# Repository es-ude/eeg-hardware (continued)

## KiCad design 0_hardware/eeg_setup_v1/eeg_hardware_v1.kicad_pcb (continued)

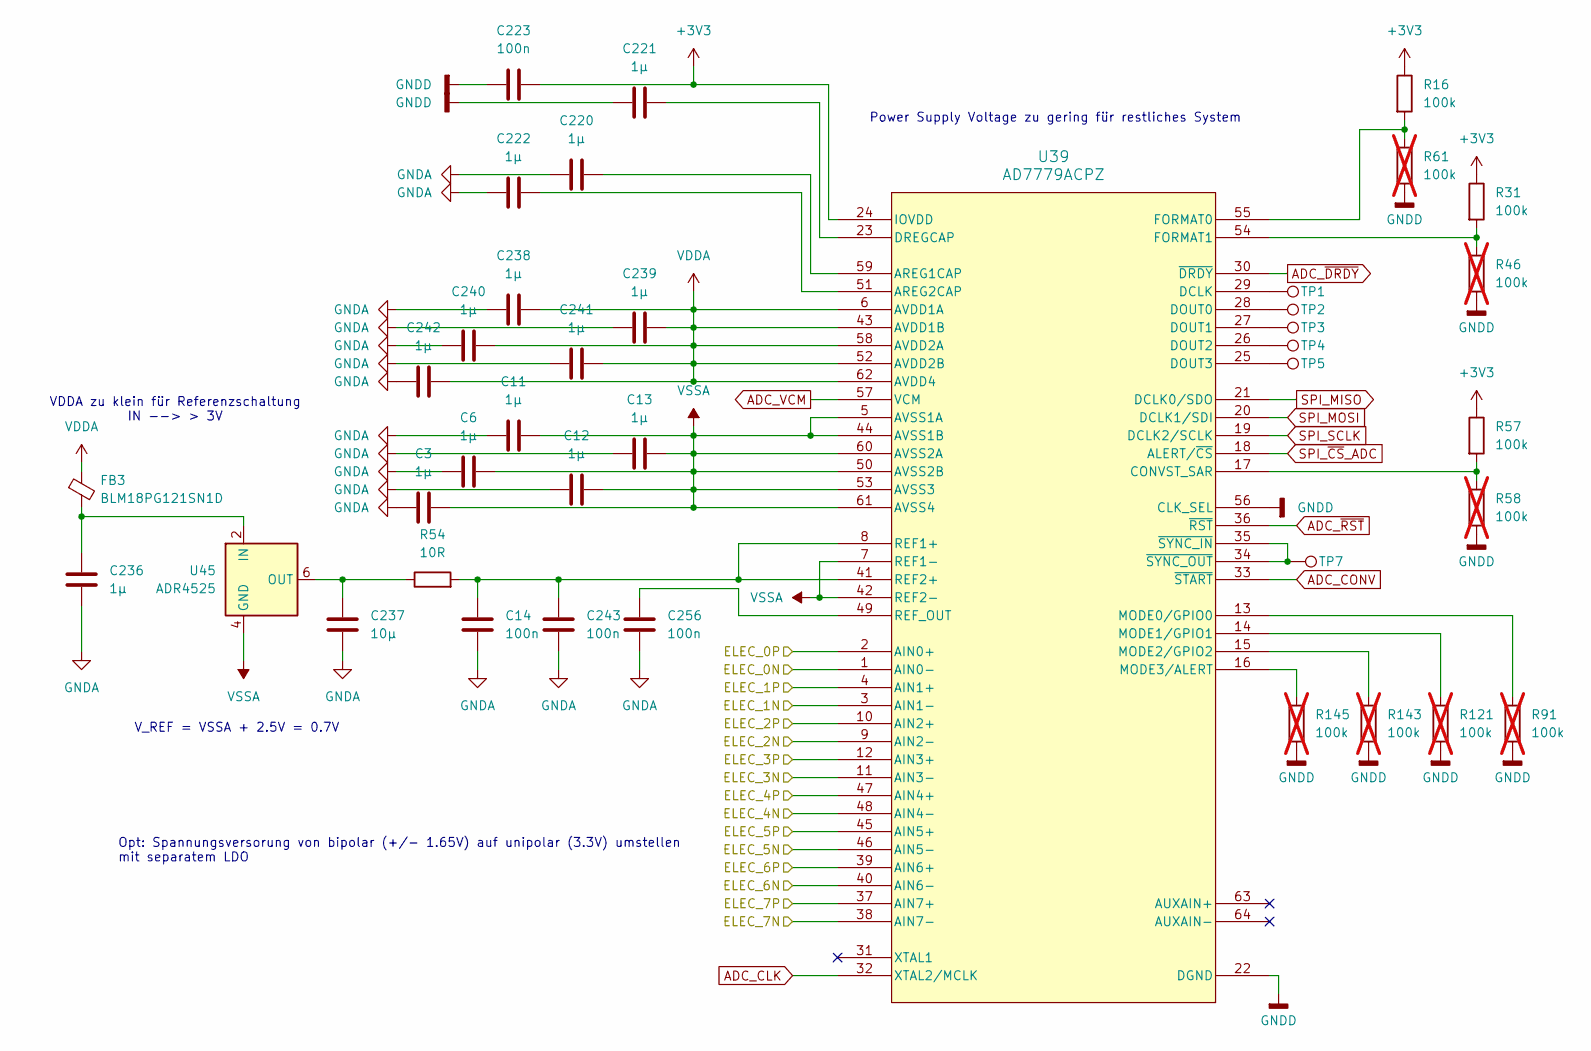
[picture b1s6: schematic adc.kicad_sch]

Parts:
C3, C6, C11, C12, C13, C220, C221, C222, C236, C238, C239, C240, C241, C242: 1µ; C_0603_1608Metric
C14, C223, C243, C256: 100n; C_0603_1608Metric
C237: 10µ; C_0603_1608Metric
FB3: FB_120Z_2A_0603; L_0603_1608Metric; MPN BLM18PG121SN1D
R16, R31, R57: 100k; R_0603_1608Metric
R46, R58, R61, R91, R121, R143, R145: 100k; R_0603_1608Metric; not fitted
R54: 10R; R_0603_1608Metric
TP1, TP2, TP3, TP4, TP5, TP7: TestPoint; TestPoint_Pad_1.5x1.5mm
U39: AD7779ACPZ; LFCSP-64-1EP_9x9mm_P0.5mm_EP5.21x5.21mm_ThermalVias
U45: ADR4525; SOIC-8_3.9x4.9mm_P1.27mm

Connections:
+3V3: C223.2, R16.1, R31.1, R57.1, U39.24 (IOVDD); also elsewhere on the board
/ADC/ELEC_0N: U39.1 (AIN0-); also elsewhere on the board
/ADC/ELEC_0P: U39.2 (AIN0+); also elsewhere on the board
/ADC/ELEC_1N: U39.3 (AIN1-); also elsewhere on the board
/ADC/ELEC_1P: U39.4 (AIN1+); also elsewhere on the board
/ADC/ELEC_2N: U39.9 (AIN2-); also elsewhere on the board
/ADC/ELEC_2P: U39.10 (AIN2+); also elsewhere on the board
/ADC/ELEC_3N: U39.11 (AIN3-); also elsewhere on the board
/ADC/ELEC_3P: U39.12 (AIN3+); also elsewhere on the board
/ADC/ELEC_4N: U39.48 (AIN4-); also elsewhere on the board
/ADC/ELEC_4P: U39.47 (AIN4+); also elsewhere on the board
/ADC/ELEC_5N: U39.46 (AIN5-); also elsewhere on the board
/ADC/ELEC_5P: U39.45 (AIN5+); also elsewhere on the board
/ADC/ELEC_6N: U39.40 (AIN6-); also elsewhere on the board
/ADC/ELEC_6P: U39.39 (AIN6+); also elsewhere on the board
/ADC/ELEC_7N: U39.38 (AIN7-); also elsewhere on the board
/ADC/ELEC_7P: U39.37 (AIN7+); also elsewhere on the board
ADC_CLK: U39.32 (XTAL2/MCLK); also elsewhere on the board
ADC_CONV: U39.33 (~START); also elsewhere on the board
ADC_VCM: U39.57 (VCM); also elsewhere on the board
ADC_~DRDY: U39.30 (~DRDY); also elsewhere on the board
ADC_~RST: U39.36 (~RST); also elsewhere on the board
GNDA: C3.1, C6.1, C11.1, C12.2, C13.2, C14.1, C220.2, C222.2, C236.2, C237.2, C238.1, C239.2, C240.1, C241.2, C242.1, C243.1, C256.1; also elsewhere on the board
GNDD: C221.2, C223.1, R46.2, R58.2, R61.2, R91.2, R121.2, R143.2, R145.2, U39.22 (DGND), U39.56 (CLK_SEL); also elsewhere on the board
unnamed: C220.1, U39.59 (AREG1CAP)
unnamed: C222.1, U39.51 (AREG2CAP)
unnamed: R57.2, R58.1, U39.17 (CONVST_SAR)
unnamed: TP1.1, U39.29 (DCLK)
unnamed: TP2.1, U39.28 (DOUT0)
unnamed: TP3.1, U39.27 (DOUT1)
unnamed: TP4.1, U39.26 (DOUT2)
unnamed: TP5.1, U39.25 (DOUT3)
unnamed: C221.1, U39.23 (DREGCAP)
unnamed: R16.2, R61.1, U39.55 (FORMAT0)
unnamed: R31.2, R46.1, U39.54 (FORMAT1)
unnamed: R91.1, U39.13 (MODE0/GPIO0)
unnamed: R121.1, U39.14 (MODE1/GPIO1)
unnamed: R143.1, U39.15 (MODE2/GPIO2)
unnamed: R145.1, U39.16 (MODE3/ALERT)
unnamed: C14.2, C243.2, R54.2, U39.8 (REF1+), U39.41 (REF2+)
unnamed: C256.2, U39.49 (REF_OUT)
unnamed: TP7.1, U39.34 (~SYNC_OUT), U39.35 (~SYNC_IN)
unnamed: C236.1, FB3.2, U45.2 (IN)
unnamed: C237.1, R54.1, U45.6 (OUT)
SPI_MISO: U39.21 (DCLK0/SDO); also elsewhere on the board
SPI_MOSI: U39.20 (DCLK1/SDI); also elsewhere on the board
SPI_SCLK: U39.19 (DCLK2/SCLK); also elsewhere on the board
SPI_~CS_ADC: U39.18 (ALERT/~CS); also elsewhere on the board
VDDA: C238.2, C239.1, C240.2, C241.1, C242.2, FB3.1, U39.6 (AVDD1A), U39.43 (AVDD1B), U39.52 (AVDD2B), U39.58 (AVDD2A), U39.62 (AVDD4); also elsewhere on the board
VSSA: C3.2, C6.2, C11.2, C12.1, C13.1, U39.5 (AVSS1A), U39.7 (REF1-), U39.42 (REF2-), U39.44 (AVSS1B), U39.50 (AVSS2B), U39.53 (AVSS3), U39.60 (AVSS2A), U39.61 (AVSS4), U39.65 (EP(GND)), U45.4 (GND); also elsewhere on the board

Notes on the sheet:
Power Supply Voltage zu gering für restliches System
Opt: Spannungsversorung von bipolar (+/- 1.65V) auf unipolar (3.3V) umstellen mit separatem LDO
VDDA zu klein für Referenzschaltung IN --> > 3V
V_REF = VSSA + 2.5V = 0.7V

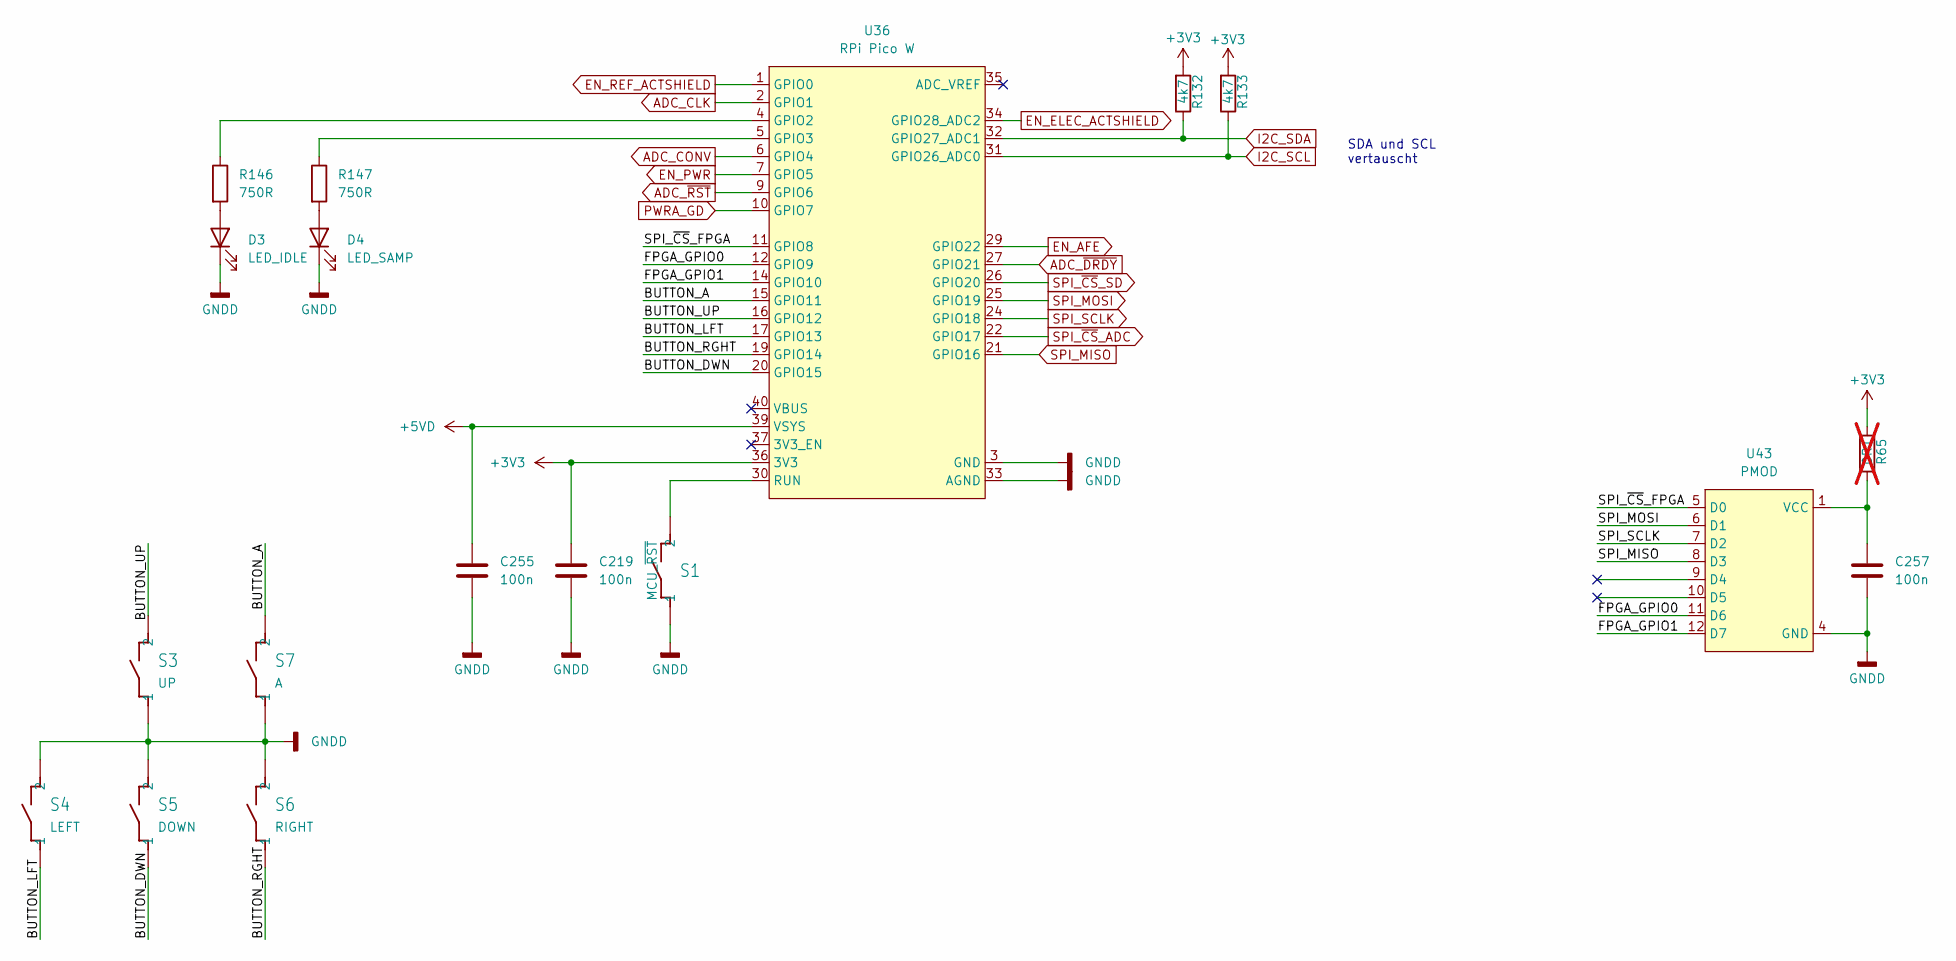
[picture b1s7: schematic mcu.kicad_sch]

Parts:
C219, C255, C257: 100n; C_0603_1608Metric
D3: LED_IDLE; LED_0603_1608Metric
D4: LED_SAMP; LED_0603_1608Metric
R65: 0R1; R_0603_1608Metric; not fitted
R132, R133: 4k7; R_0603_1608Metric
R146, R147: 750R; R_0603_1608Metric
S1: MCU_~{RST}; TACTILE-SWITCH
S3: UP; TACTILE-SWITCH
S4: LEFT; TACTILE-SWITCH
S5: DOWN; TACTILE-SWITCH
S6: RIGHT; TACTILE-SWITCH
S7: A; TACTILE-SWITCH
U36: RPi Pico W; RPi_PicoW
U43: PMOD; PinHeader_2x06_P2.54mm_Horizontal

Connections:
+3V3: C219.1, R65.2, R132.2, R133.2, U36.36 (3V3); also elsewhere on the board
+5VD: C255.1, U36.39 (VSYS); also elsewhere on the board
/MCU/BUTTON_A: S7.3 (2), S7.4 (2), U36.15 (GPIO11)
/MCU/BUTTON_DWN: S5.1, S5.2 (1), U36.20 (GPIO15)
/MCU/BUTTON_LFT: S4.1, S4.2 (1), U36.17 (GPIO13)
/MCU/BUTTON_RGHT: S6.1, S6.2 (1), U36.19 (GPIO14)
/MCU/BUTTON_UP: S3.3 (2), S3.4 (2), U36.16 (GPIO12)
/MCU/FPGA_GPIO0: U36.12 (GPIO9), U43.11 (D6)
/MCU/FPGA_GPIO1: U36.14 (GPIO10), U43.12 (D7)
/MCU/SPI_~CS_FPGA: U36.11 (GPIO8), U43.5 (D0)
ADC_CLK: U36.2 (GPIO1); also elsewhere on the board
ADC_CONV: U36.6 (GPIO4); also elsewhere on the board
ADC_~DRDY: U36.27 (GPIO21); also elsewhere on the board
ADC_~RST: U36.9 (GPIO6); also elsewhere on the board
EN_AFE: U36.29 (GPIO22); also elsewhere on the board
EN_ELEC_ACTSHIELD: U36.34 (GPIO28_ADC2); also elsewhere on the board
EN_PWR: U36.7 (GPIO5); also elsewhere on the board
EN_REF_ACTSHIELD: U36.1 (GPIO0); also elsewhere on the board
GNDD: C219.2, C255.2, C257.2, D3.1 (K), D4.1 (K), S1.1, S1.2 (1), S3.1, S3.2 (1), S4.3 (2), S4.4 (2), S5.3 (2), S5.4 (2), S6.3 (2), S6.4 (2), S7.1, S7.2 (1), U36.3 (GND), U36.8 (GND), U36.13 (GND), U36.18 (GND), U36.23 (GND), U36.28 (GND), U36.33 (AGND), U36.38 (GND), U43.3 (GND), U43.4 (GND); also elsewhere on the board
I2C_SCL: R133.1, U36.31 (GPIO26_ADC0); also elsewhere on the board
I2C_SDA: R132.1, U36.32 (GPIO27_ADC1); also elsewhere on the board
unnamed: C257.1, R65.1, U43.1 (VCC), U43.2 (VCC)
unnamed: D3.2 (A), R146.2
unnamed: D4.2 (A), R147.2
unnamed: R146.1, U36.4 (GPIO2)
unnamed: R147.1, U36.5 (GPIO3)
unnamed: S1.3 (2), S1.4 (2), U36.30 (RUN)
PWRA_GD: U36.10 (GPIO7); also elsewhere on the board
SPI_MISO: U36.21 (GPIO16), U43.8 (D3); also elsewhere on the board
SPI_MOSI: U36.25 (GPIO19), U43.6 (D1); also elsewhere on the board
SPI_SCLK: U36.24 (GPIO18), U43.7 (D2); also elsewhere on the board
SPI_~CS_ADC: U36.22 (GPIO17); also elsewhere on the board
SPI_~CS_SD: U36.26 (GPIO20); also elsewhere on the board

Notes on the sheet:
SDA und SCL vertauscht

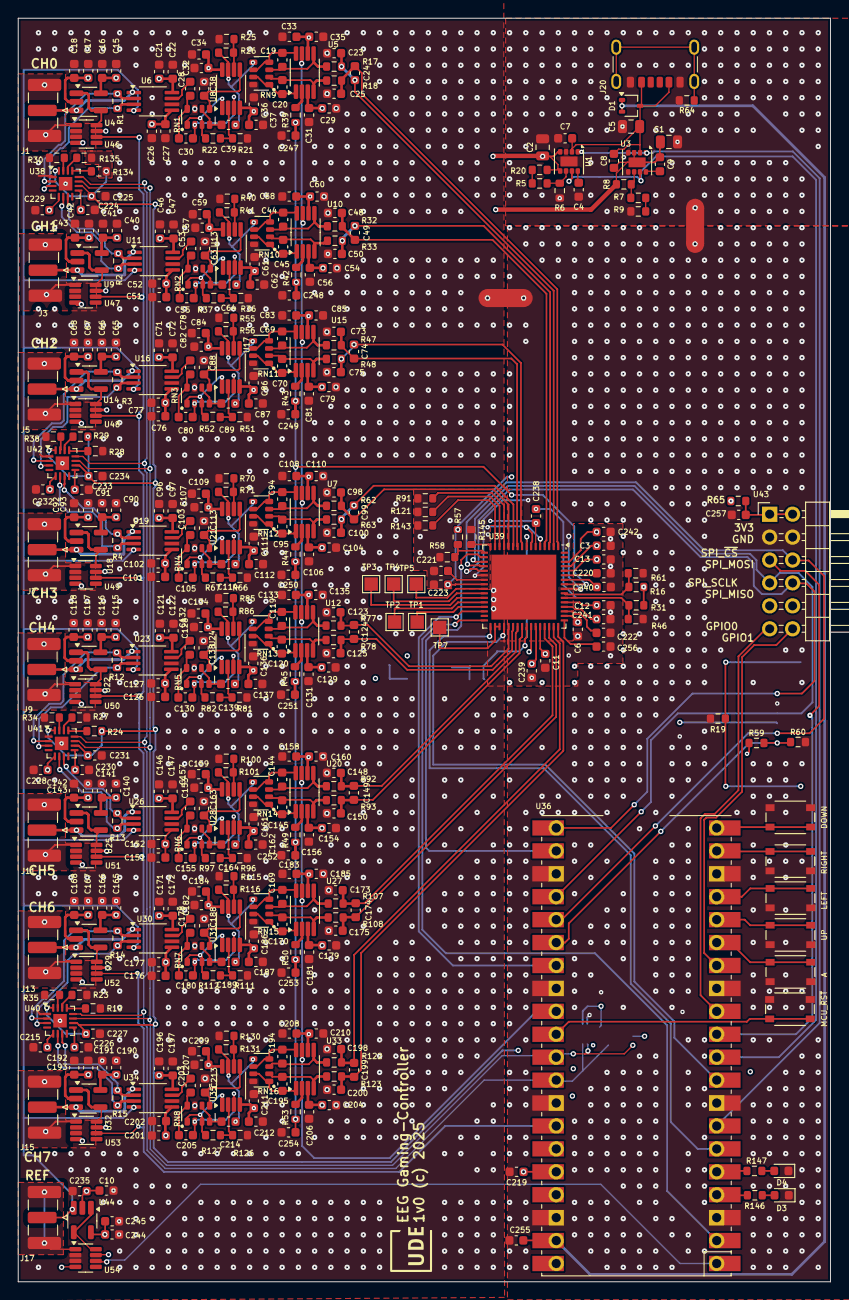
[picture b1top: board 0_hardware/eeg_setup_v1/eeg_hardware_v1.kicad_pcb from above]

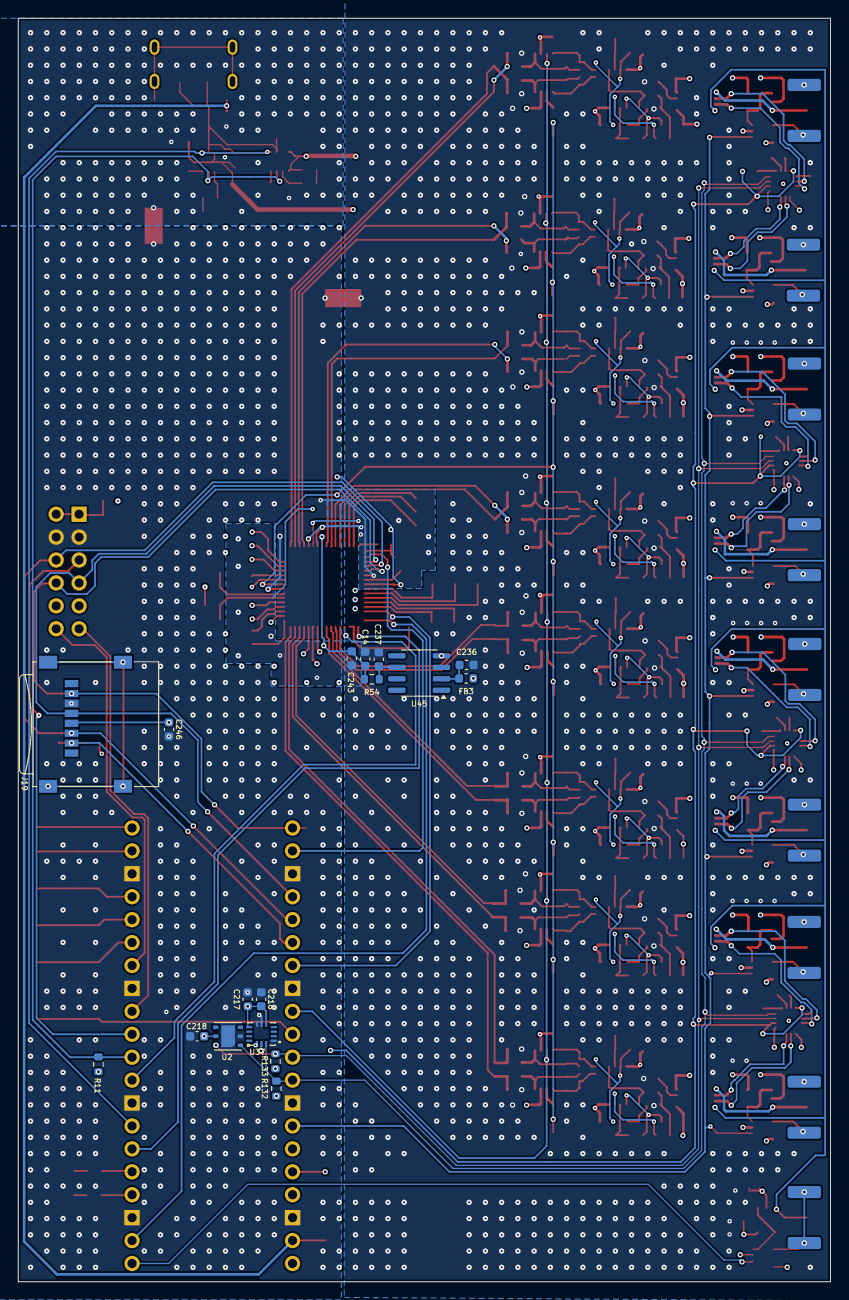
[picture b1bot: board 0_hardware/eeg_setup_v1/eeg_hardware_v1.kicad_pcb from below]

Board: 4 copper layers, 90.0 x 140.0 mm, 459 parts (17 on the bottom side), 250 nets.

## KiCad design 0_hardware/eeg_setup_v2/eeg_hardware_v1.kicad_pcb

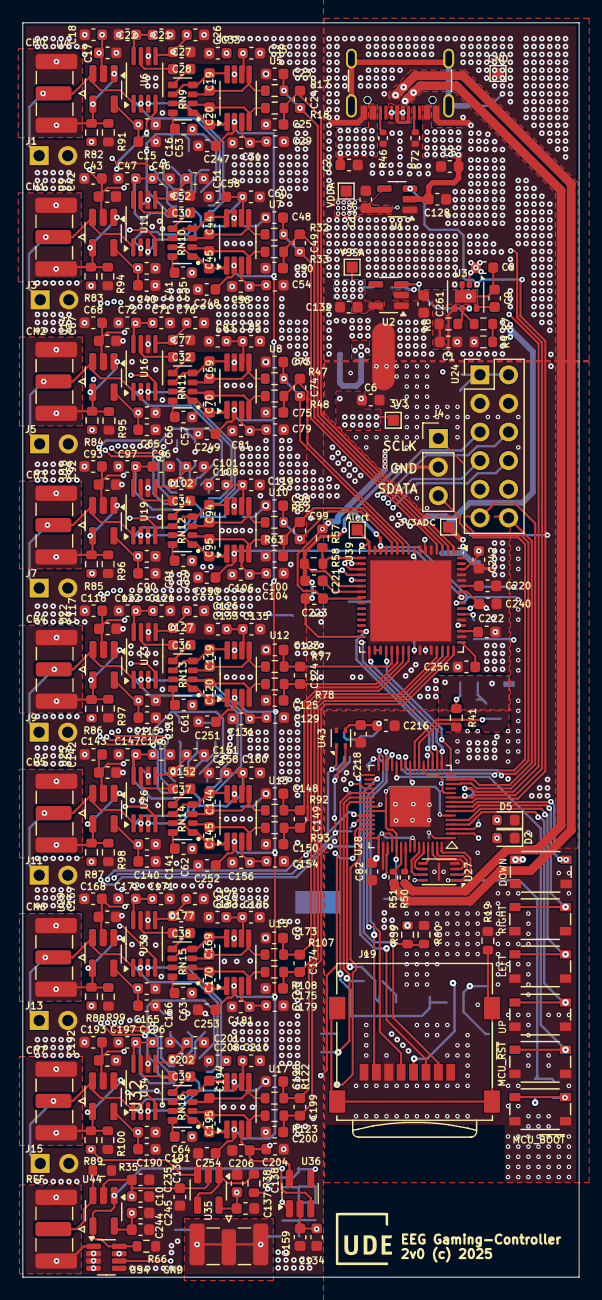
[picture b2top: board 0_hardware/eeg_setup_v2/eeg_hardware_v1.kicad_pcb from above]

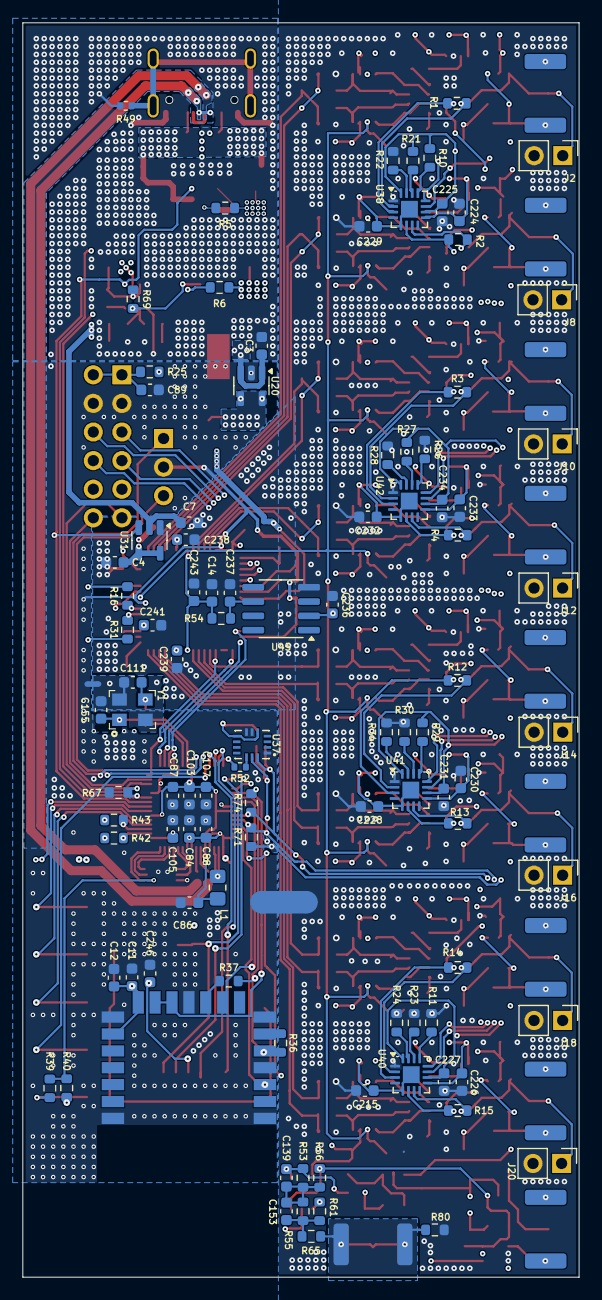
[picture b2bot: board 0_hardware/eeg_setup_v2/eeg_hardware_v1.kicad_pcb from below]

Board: 4 copper layers, 49.4 x 111.4 mm, 411 parts (102 on the bottom side), 208 nets.

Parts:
C1, C2, C5: 22µ; C_0603_1608Metric
C3, C6, C9, C11, C12, C14, C16, C18, C22, C27, C31, C35, C41, C43, C47, C52, C56, C60, C66, C68, C72, C77, C81, C84, C85, C87, C88, C89, C91, C93, C97, C102, C103, C105, C106, C107, C110, C116, C118, C122, C127, C131, C135, C136, C137, C139, C141, C143, C147, C152, C156, C159, C160, C166, C168, C172, C177, C181, C185, C191, C193, C197, C202, C206, C210, C215, C216, C218, C223, C224, C225, C226, C227, C228, C229, C230, C231, C232, C233, C234, C235, C243, C244, C246, C247, C248, C249, C250, C251, C252, C253, C254, C256: 100n; C_0603_1608Metric
C4, C7, C8, C10, C15, C17, C21, C26, C40, C42, C46, C51, C65, C67, C71, C76, C82, C86, C90, C92, C96, C101, C114, C115, C117, C121, C126, C128, C132, C134, C138, C140, C142, C146, C151, C165, C167, C171, C176, C190, C192, C196, C201, C237, C245, C261: 10µ; C_0603_1608Metric
C19, C20, C44, C45, C69, C70, C94, C95, C119, C120, C144, C145, C169, C170, C194, C195: 1n; C_0603_1608Metric
C23, C24, C25, C48, C49, C50, C73, C74, C75, C98, C99, C100, C123, C124, C125, C148, C149, C150, C173, C174, C175, C198, C199, C200: 100p; C_0603_1608Metric
C28, C30, C32, C34, C36, C37, C38, C39, C53, C55, C57, C59, C61, C62, C63, C64: 68µ; C_0603_1608Metric
C29, C33, C54, C58, C79, C83, C104, C108, C129, C133, C154, C158, C179, C183, C204, C208: 10u; C_0603_1608Metric
C111, C155: 22p; C_0603_1608Metric
C153: 10n; C_0603_1608Metric
C220, C221, C222, C236, C238, C239, C240, C241, C242: 1µ; C_0603_1608Metric
D2: LED_IDLE; LED_0603_1608Metric
D5: LED_SAMP; LED_0603_1608Metric
J1, J3, J5, J7, J9, J11, J13, J15, J17, J21: SMA-FEMALE-H; SMA_Samtec_SMA-J-P-H-ST-EM1_EdgeMount
J2, J8, J10, J12, J14, J16, J18, J20: PIN-MALE-H; PinHeader_1x02_P2.54mm_Vertical
J4: Pico Debugger (SWD); PinHeader_1x03_P2.54mm_Vertical
J6: USB-C Receptable (16P); USB_C_Receptacle_16P
J19: Micro_SD_Card; microSD_HC_Wuerth_693072010801
L1: 3µ3; R_0805_2012Metric_Pad1.20x1.40mm_HandSolder
NT1, NT2: NetTie_2; NetTie-2_SMD_Pad2.0mm
NT3: NetTie_2; NetTie-2_SMD_Pad0.5mm
R1, R2, R3, R4, R7, R12, R13, R14, R15: 1k; R_0603_1608Metric
R5, R6, R8, R40, R59, R60, R67, R69, R82, R83, R84, R85, R86, R87, R88, R89: 10k; R_0603_1608Metric
R9: 22k; R_0603_1608Metric
R10, R11, R21, R22, R23, R24, R26, R27, R28, R29, R30, R34, R57, R58: 4k7; R_0603_1608Metric
R16, R31, R71, R74: 5k1; R_0603_1608Metric
R17, R18, R32, R33, R47, R48, R62, R63, R77, R78, R92, R93, R107, R108, R122, R123: 100R; R_0603_1608Metric
R19, R36, R39, R41, R42, R43: 750R; R_0603_1608Metric
R25, R35, R54, R65, R66, R80, R91, R94, R95, R96, R97, R98, R99, R100: 0R1; R_0603_1608Metric
R37: 100k; R_0603_1608Metric
R38, R56, R61: 1k5; R_0603_1608Metric
R46, R49, R52, R72: 5k1; R_0402_1005Metric
R50, R51: 27R; R_0402_1005Metric
R53, R55: 160k; R_0603_1608Metric
RN9, RN10, RN11, RN12, RN13, RN14, RN15, RN16: 22k; RES_YC164_CAXE80P320X160X70
S2: MCU_~{BOOT}; TACTILE-SWITCH
S3: UP; TACTILE-SWITCH
S4: LEFT; TACTILE-SWITCH
S5: DOWN; TACTILE-SWITCH
S6: RIGHT; TACTILE-SWITCH
S8: MCU_~{RST}; TACTILE-SWITCH
TP1: Alert; TestPoint_Pad_1.0x1.0mm
TP2: VSSA; TestPoint_Pad_1.0x1.0mm
TP3: 3V3; TestPoint_Pad_1.0x1.0mm
TP4: GND; TestPoint_Pad_1.0x1.0mm
TP5: 3V3ADC; TestPoint_Pad_1.0x1.0mm
TP8: VDDA; TestPoint_Pad_1.0x1.0mm
U1: ADP7142AUJZ-2.5; TSOT-23-5
U2: ADP7182AUJZ-2.5; TSOT-23-5
U3: TPS82150; Texas_SIL0008D_MicroSiP-8-1EP_2.8x3mm_P0.65mm_EP1.1x1.9mm
U4, U9, U14, U18, U22, U25, U29, U32, U35, U36: LTC2054HV; SOT-23-5_HandSoldering
U5, U7, U8, U10, U12, U13, U15, U17: OPA1637; VSSOP-8_3x3mm_P0.65mm
U6, U11, U16, U19, U23, U26, U30, U34: AD8422ARMZ; MSOP-8_3x3mm_P0.65mm
U20, U31: ADP7142AUJZ-3.3; TSOT-23-5
U21: Pi-Radio; RPi-Radio-Module
U24: PMOD; PinHeader_2x06_P2.54mm_Vertical
U27: W25Q16JVUXIQ; USON-8-1EP_3x2mm_P0.5mm_EP0.2x1.6mm
U28: RP235xA; QFN-60_EP_7x7_Pitch0.4mm
U37: BMI270; XDCR_BMI270
U38, U40, U41, U42: AD5142A-100k; LFCSP-16-1EP_3x3mm_P0.5mm_EP1.5x1.5mm
U39: AD7779ACPZ; LFCSP-64-1EP_9x9mm_P0.5mm_EP5.21x5.21mm_ThermalVias
U43: SHT41; Sensirion_DFN-4_1.5x1.5mm_P0.8mm_SHT4x_NoCentralPad
U44: OPA145_SOT; SOT-23-5_HandSoldering
U45: ADR4525; SOIC-8_3.9x4.9mm_P1.27mm
U54: TS12A12511; SOT-23-8
Y1: KX7_QRZ; KX-7

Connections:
+1V1: C86.2, C87.2, C103.2, C107.2, L1.1, U28.6 (DVDD_1V1), U28.23 (DVDD_1V1), U28.39 (DVDD_1V1), U28.50 (VREG_FB)
+3.3VADC: C4.1, C238.2, C239.1, C240.2, C241.1, C242.2, TP5.1, U31.4 (SENSE), U31.5 (VOUT), U39.6 (AVDD1A), U39.43 (AVDD1B), U39.52 (AVDD2B), U39.58 (AVDD2A), U39.62 (AVDD4)
+3V3: C6.1, C11.1, C12.1, C82.2, C84.2, C88.2, C105.2, C216.1, C218.1, C223.2, C225.1, C227.1, C231.1, C234.1, C246.1, J19.4 (VDD), R10.1, R16.1, R21.1, R25.2, R27.1, R29.1, R31.1, R40.2, R52.1, R57.1, R59.1, R71.2, R74.2, TP3.1, U20.4 (SENSE/ADJ), U20.5 (VOUT), U21.14 (VDDIO), U21.16 (VIN), U27.8 (VCC), U28.1 (IOVDD), U28.11 (IOVDD), U28.20 (IOVDD), U28.30 (IOVDD), U28.38 (IOVDD), U28.44 (AVDD_ADC), U28.45 (IOVDD), U28.46 (VREG_AVDD), U28.49 (VREG_IN), U28.53 (USB_OTP_VDD), U28.54 (IOVDD_QSPI), U37.5 (VDDIO), U37.8 (VDD), U38.10 (V_LOGIC), U38.16 (~RST), U39.24 (IOVDD), U40.10 (V_LOGIC), U40.16 (~RST), U41.10 (V_LOGIC), U41.16 (~RST), U42.10 (V_LOGIC), U42.16 (~RST), U43.3 (VDD)
/ADC/ELEC_0N: C24.2, C25.1, R18.2, U39.1 (AIN0-)
/ADC/ELEC_0P: C23.2, C24.1, R17.2, U39.2 (AIN0+)
/ADC/ELEC_1N: C49.2, C50.1, R33.2, U39.3 (AIN1-)
/ADC/ELEC_1P: C48.2, C49.1, R32.2, U39.4 (AIN1+)
/ADC/ELEC_2N: C74.2, C75.1, R48.2, U39.9 (AIN2-)
/ADC/ELEC_2P: C73.2, C74.1, R47.2, U39.10 (AIN2+)
/ADC/ELEC_3N: C99.2, C100.1, R63.2, U39.11 (AIN3-)
/ADC/ELEC_3P: C98.2, C99.1, R62.2, U39.12 (AIN3+)
/ADC/ELEC_4N: C199.2, C200.1, R123.2, U39.48 (AIN4-)
/ADC/ELEC_4P: C198.2, C199.1, R122.2, U39.47 (AIN4+)
/ADC/ELEC_5N: C174.2, C175.1, R108.2, U39.46 (AIN5-)
/ADC/ELEC_5P: C173.2, C174.1, R107.2, U39.45 (AIN5+)
/ADC/ELEC_6N: C149.2, C150.1, R93.2, U39.40 (AIN6-)
/ADC/ELEC_6P: C148.2, C149.1, R92.2, U39.39 (AIN6+)
/ADC/ELEC_7N: C124.2, C125.1, R78.2, U39.38 (AIN7-)
/ADC/ELEC_7P: C123.2, C124.1, R77.2, U39.37 (AIN7+)
/EEG Frontend CH0/ELEC_FB: J1.2 (GND), R82.2, R91.1, U4.1, U4.4 (-)
/EEG Frontend CH0/Rg_PinN: R1.1, U6.3 (Rg), U38.3 (W1)
/EEG Frontend CH0/Rg_PinP: R1.2, U6.2 (Rg), U38.2 (A1)
/EEG Frontend CH1/ELEC_FB: J3.2 (GND), R83.2, R94.1, U9.1, U9.4 (-)
/EEG Frontend CH1/Rg_PinN: R2.1, U11.3 (Rg), U38.6 (A2)
/EEG Frontend CH1/Rg_PinP: R2.2, U11.2 (Rg), U38.7 (W2)
/EEG Frontend CH2/ELEC_FB: J5.2 (GND), R84.2, R95.1, U14.1, U14.4 (-)
/EEG Frontend CH2/Rg_PinN: R3.1, U16.3 (Rg), U42.3 (W1)
/EEG Frontend CH2/Rg_PinP: R3.2, U16.2 (Rg), U42.2 (A1)
/EEG Frontend CH3/ELEC_FB: J7.2 (GND), R85.2, R96.1, U18.1, U18.4 (-)
/EEG Frontend CH3/Rg_PinN: R4.1, U19.3 (Rg), U42.6 (A2)
/EEG Frontend CH3/Rg_PinP: R4.2, U19.2 (Rg), U42.7 (W2)
/EEG Frontend CH4/ELEC_FB: J9.2 (GND), R86.2, R97.1, U22.1, U22.4 (-)
/EEG Frontend CH4/Rg_PinN: R12.1, U23.3 (Rg), U41.3 (W1)
/EEG Frontend CH4/Rg_PinP: R12.2, U23.2 (Rg), U41.2 (A1)
/EEG Frontend CH5/ELEC_FB: J11.2 (GND), R87.2, R98.1, U25.1, U25.4 (-)
/EEG Frontend CH5/Rg_PinN: R13.1, U26.3 (Rg), U41.6 (A2)
/EEG Frontend CH5/Rg_PinP: R13.2, U26.2 (Rg), U41.7 (W2)
/EEG Frontend CH6/ELEC_FB: J13.2 (GND), R88.2, R99.1, U29.1, U29.4 (-)
/EEG Frontend CH6/Rg_PinN: R14.1, U30.3 (Rg), U40.3 (W1)
/EEG Frontend CH6/Rg_PinP: R14.2, U30.2 (Rg), U40.2 (A1)
/EEG Frontend CH7/ELEC_FB: J15.2 (GND), R89.2, R100.1, U32.1, U32.4 (-)
/EEG Frontend CH7/Rg_PinN: R15.1, U34.3 (Rg), U40.6 (A2)
/EEG Frontend CH7/Rg_PinP: R15.2, U34.2 (Rg), U40.7 (W2)
/MCU/BUTTON_DWN: S5.1, S5.2 (1), U28.8 (GPIO_05)
/MCU/BUTTON_LFT: S4.1, S4.2 (1), U28.5 (GPIO_03)
/MCU/BUTTON_RGHT: S6.1, S6.2 (1), U28.7 (GPIO_04)
/MCU/BUTTON_UP: S3.3 (2), S3.4 (2), U28.4 (GPIO_02)
/MCU/FPGA_GPIO0: U24.11 (D6), U28.13 (GPIO_09)
/MCU/FPGA_GPIO1: U24.12 (D7), U28.14 (GPIO_10)
/MCU/GND_QRZ: C111.2, C155.2, NT3.2, Y1.2 (SH), Y1.4 (SH)
/MCU/SPI_~CS_FPGA: U24.5 (D0), U28.34 (GPIO_22)
/MCU/WL_DATA: R36.2, R37.2, U21.5 (SDI), U28.36 (GPIO_24)
/MCU/WL_EN: U21.12 (WL_ON), U21.13 (BT_ON), U28.35 (GPIO_23)
/MCU/WL_SCLK: U21.3 (SCLK), U28.43 (GPIO_29_ADC3)
/MCU/WL_~CS: U21.9 (~CS), U28.37 (GPIO_25)
/Power/VSS_UNBUF: C1.2, C8.2, C9.2, C261.1, R8.2, R69.1, U2.2 (VIN), U3.3 (GND), U3.9 (GND)
ADC_ALERT: TP1.1, U28.19 (GPIO_15), U39.16 (MODE3/ALERT)
ADC_CLK: U28.17 (GPIO_13), U39.32 (XTAL2/MCLK)
ADC_CONV: U28.16 (GPIO_12), U39.33 (~START)
ADC_VCM: C247.1, C248.1, C249.1, C250.1, C251.1, C252.1, C253.1, C254.1, U5.2 (V_{OCM}), U7.2 (V_{OCM}), U8.2 (V_{OCM}), U10.2 (V_{OCM}), U12.2 (V_{OCM}), U13.2 (V_{OCM}), U15.2 (V_{OCM}), U17.2 (V_{OCM}), U39.57 (VCM)
ADC_~DRDY: U28.18 (GPIO_14), U39.30 (~DRDY)
ADC_~RST: U28.15 (GPIO_11), U39.36 (~RST)
ELEC_DRIVE: R82.1, R83.1, R84.1, R85.1, R86.1, R87.1, R88.1, R89.1, U35.3 (+)
ELEC_REF: R56.2, R66.2, U6.4 (+), U11.4 (+), U16.4 (+), U19.4 (+), U23.4 (+), U26.4 (+), U30.4 (+), U34.4 (+), U36.3 (+), U44.1, U44.4 (-), U54.8
EN_PWR: U1.3 (EN), U3.1 (EN), U28.9 (GPIO_06), U31.3 (EN)
EN_REF_ACTSHIELD: U28.42 (GPIO_28_ADC2), U54.6
GND: C1.1, C2.2, C3.2, C5.2, C114.2, C128.2, C132.2, C261.2, J6.A1 (GND), J6.A12 (GND), J6.B1 (GND), J6.B12 (GND), NT1.2, R9.2, R46.2, R49.2, R72.2, TP4.1, U1.1 (GND), U2.1 (GND), U3.4 (VOUT), U3.5 (VOUT)
GNDA: C4.2, C7.2, C10.2, C14.1, C15.2, C16.2, C17.2, C18.2, C21.2, C22.2, C23.1, C25.2, C26.2, C27.2, C29.2, C31.2, C33.2, C35.2, C40.2, C41.2, C42.2, C43.2, C46.2, C47.2, C48.1, C50.2, C51.2, C52.2, C53.2, C54.2, C55.2, C56.2, C57.2, C58.2, C59.2, C60.2, C61.2, C62.2, C63.2, C64.2, C65.2, C66.2, C67.2, C68.2, C71.2, C72.2, C73.1, C75.2, C76.2, C77.2, C79.2, C81.2, C83.2, C85.2, C90.2, C91.2, C92.2, C93.2, C96.2, C97.2, C98.1, C100.2, C101.2, C102.2, C104.2, C106.2, C108.2, C110.2, C115.2, C116.2, C117.2, C118.2, C121.2, C122.2, C123.1, C125.2, C126.2, C127.2, C129.2, C131.2, C133.2, C134.2, C135.2, C136.2, C137.2, C138.2, C140.2, C141.2, C142.2, C143.2, C146.2, C147.2, C148.1, C150.2, C151.2, C152.2, C154.2, C156.2, C158.2, C159.2, C160.2, C165.2, C166.2, C167.2, C168.2, C171.2, C172.2, C173.1, C175.2, C176.2, C177.2, C179.2, C181.2, C183.2, C185.2, C190.2, C191.2, C192.2, C193.2, C196.2, C197.2, C198.1, C200.2, C201.2, C202.2, C204.2, C206.2, C208.2, C210.2, C215.1, C220.2, C222.2, C224.2, C225.2, C226.2, C227.2, C228.1, C229.1, C230.2, C231.2, C232.1, C233.2, C234.2, C235.2, C236.2, C237.2, C238.1, C239.2, C240.1, C241.2, C242.1, C243.1, C244.2, C245.2, C247.2, C248.2, C249.2, C250.2, C251.2, C252.2, C253.2, C254.2, C256.1, J2.2 (GND), J8.2 (GND), J10.2 (GND), J12.2 (GND), J14.2 (GND), J16.2 (GND), J18.2 (GND), J20.2 (GND), NT2.2, R11.1, R22.1, R23.1, R24.1, R26.1, R28.1, R30.1, R34.1, R35.1, R66.1, R80.1, R91.2, R94.2, R95.2, R96.2, R97.2, R98.2, R99.2, R100.2, U6.6 (Ref), U11.6 (Ref), U16.6 (Ref), U19.6 (Ref), U23.6 (Ref), U26.6 (Ref), U30.6 (Ref), U31.1 (GND), U34.6 (Ref), U38.1 (GND), U39.5 (AVSS1A), U39.7 (REF1-), U39.42 (REF2-), U39.44 (AVSS1B), U39.50 (AVSS2B), U39.53 (AVSS3), U39.60 (AVSS2A), U39.61 (AVSS4), U39.65 (EP(GND)), U40.1 (GND), U41.1 (GND), U42.1 (GND), U45.4 (GND), U54.2, U54.3 (GND)
GNDD: C6.2, C11.2, C12.2, C82.1, C84.1, C86.1, C87.1, C88.1, C89.2, C103.1, C105.1, C107.1, C216.2, C218.2, C221.2, C223.1, C246.2, D2.1 (K), D5.1 (K), J4.2 (GND), J19.6 (VSS), NT1.1, NT2.1, NT3.1, R19.2, R58.2, R60.2, R67.1, S2.1, S2.2 (1), S3.1, S3.2 (1), S4.3 (2), S4.4 (2), S5.3 (2), S5.4 (2), S6.3 (2), S6.4 (2), S8.1, S8.2 (1), U20.2 (GND), U21.1 (GND), U21.4 (GND), U21.7 (GND), U21.11 (GND), U21.15 (GND), U21.21 (GND), U24.3 (GND), U24.4 (GND), U27.4 (VSS), U27.9 (VSS), U28.47 (GND), U28.61 (GND), U37.1 (SDO), U37.6 (GNDIO), U37.7 (GND), U39.13 (MODE0/GPIO0), U39.14 (MODE1/GPIO1), U39.15 (MODE2/GPIO2), U39.22 (DGND), U39.31 (XTAL1), U39.56 (CLK_SEL), U43.4 (VSS)
I2C_SCL: R71.1, U28.41 (GPIO_27_ADC1), U37.13 (SCX), U38.11 (SCL), U40.11 (SCL), U41.11 (SCL), U42.11 (SCL), U43.2 (SCL)
I2C_SDA: R74.1, U28.40 (GPIO_26_ADC0), U37.14 (SDX), U38.12 (SDA), U40.12 (SDA), U41.12 (SDA), U42.12 (SDA), U43.1 (SDA)
unnamed: C28.2, U6.7
unnamed: C30.2, U11.7
unnamed: C32.2, U16.7
unnamed: C34.2, U19.7
unnamed: C36.2, U23.7
unnamed: C37.2, U26.7
unnamed: C38.2, U30.7
unnamed: C39.2, U34.7
unnamed: C89.1, R25.1, U24.1 (VCC), U24.2 (VCC)
unnamed: C111.1, R41.1, Y1.3
unnamed: C139.2, C153.1, R53.1, R55.2, R56.1
unnamed: C153.2, R55.1, R61.1, R65.2
unnamed: D2.2 (A), R42.2
unnamed: D5.2 (A), R43.2
unnamed: J1.1 (SIG), J2.1 (SIG), U4.3 (+), U6.1 (-)
unnamed: J3.1 (SIG), J8.1 (SIG), U9.3 (+), U11.1 (-)
unnamed: J4.1 (SCLK), U28.24 (SWCLK)
unnamed: J4.3 (SDATA), U28.25 (SWDIO)
unnamed: J6.A5 (CC1), R72.1
unnamed: J6.B5 (CC2), R46.1
unnamed: J6.S1 (SHIELD), R49.1
unnamed: J5.1 (SIG), J10.1 (SIG), U14.3 (+), U16.1 (-)
unnamed: J11.1 (SIG), J16.1 (SIG), U25.3 (+), U26.1 (-)
unnamed: J7.1 (SIG), J12.1 (SIG), U18.3 (+), U19.1 (-)
unnamed: J13.1 (SIG), J18.1 (SIG), U29.3 (+), U30.1 (-)
unnamed: J9.1 (SIG), J14.1 (SIG), U22.3 (+), U23.1 (-)
unnamed: J15.1 (SIG), J20.1 (SIG), U32.3 (+), U34.1 (-)
unnamed: J17.2 (GND), U54.1 (COM)
unnamed: J17.1 (SIG), R35.2, U44.3 (+)
unnamed: J19.9 (SHIELD), R19.1
unnamed: J21.1 (SIG), J21.2 (GND), R65.1, R80.2
unnamed: R7.1, R9.1
unnamed: R39.2, S2.3 (2), S2.4 (2)
unnamed: R61.2, U36.1
unnamed: C20.1, RN9.1 (R1.1), RN9.7 (R2.2), U5.1 (-)
unnamed: C53.1, RN9.8 (R1.2)
unnamed: C20.2, R18.1, RN9.2 (R2.1), U5.4
unnamed: C19.2, R17.1, RN9.3 (R3.1), U5.5
unnamed: C19.1, RN9.4 (R4.1), RN9.6 (R3.2), U5.8 (+)
unnamed: C28.1, RN9.5 (R4.2)
unnamed: C45.1, RN10.1 (R1.1), RN10.7 (R2.2), U7.1 (-)
unnamed: C55.1, RN10.8 (R1.2)
unnamed: C45.2, R33.1, RN10.2 (R2.1), U7.4
unnamed: C44.2, R32.1, RN10.3 (R3.1), U7.5
unnamed: C44.1, RN10.4 (R4.1), RN10.6 (R3.2), U7.8 (+)
unnamed: C30.1, RN10.5 (R4.2)
unnamed: C70.1, RN11.1 (R1.1), RN11.7 (R2.2), U8.1 (-)
unnamed: C57.1, RN11.8 (R1.2)
unnamed: C70.2, R48.1, RN11.2 (R2.1), U8.4
unnamed: C69.2, R47.1, RN11.3 (R3.1), U8.5
unnamed: C69.1, RN11.4 (R4.1), RN11.6 (R3.2), U8.8 (+)
unnamed: C32.1, RN11.5 (R4.2)
unnamed: C95.1, RN12.1 (R1.1), RN12.7 (R2.2), U10.1 (-)
unnamed: C59.1, RN12.8 (R1.2)
unnamed: C95.2, R63.1, RN12.2 (R2.1), U10.4
unnamed: C94.2, R62.1, RN12.3 (R3.1), U10.5
unnamed: C94.1, RN12.4 (R4.1), RN12.6 (R3.2), U10.8 (+)
unnamed: C34.1, RN12.5 (R4.2)
unnamed: C120.1, RN13.1 (R1.1), RN13.7 (R2.2), U12.1 (-)
unnamed: C61.1, RN13.8 (R1.2)
unnamed: C120.2, R78.1, RN13.2 (R2.1), U12.4
unnamed: C119.2, R77.1, RN13.3 (R3.1), U12.5
unnamed: C119.1, RN13.4 (R4.1), RN13.6 (R3.2), U12.8 (+)
unnamed: C36.1, RN13.5 (R4.2)
unnamed: C145.1, RN14.1 (R1.1), RN14.7 (R2.2), U13.1 (-)
unnamed: C62.1, RN14.8 (R1.2)
unnamed: C145.2, R93.1, RN14.2 (R2.1), U13.4
unnamed: C144.2, R92.1, RN14.3 (R3.1), U13.5
unnamed: C144.1, RN14.4 (R4.1), RN14.6 (R3.2), U13.8 (+)
unnamed: C37.1, RN14.5 (R4.2)
unnamed: C170.1, RN15.1 (R1.1), RN15.7 (R2.2), U15.1 (-)
unnamed: C63.1, RN15.8 (R1.2)
unnamed: C170.2, R108.1, RN15.2 (R2.1), U15.4
unnamed: C169.2, R107.1, RN15.3 (R3.1), U15.5
unnamed: C169.1, RN15.4 (R4.1), RN15.6 (R3.2), U15.8 (+)
unnamed: C38.1, RN15.5 (R4.2)
unnamed: C195.1, RN16.1 (R1.1), RN16.7 (R2.2), U17.1 (-)
unnamed: C64.1, RN16.8 (R1.2)
unnamed: C195.2, R123.1, RN16.2 (R2.1), U17.4
unnamed: C194.2, R122.1, RN16.3 (R3.1), U17.5
unnamed: C194.1, RN16.4 (R4.1), RN16.6 (R3.2), U17.8 (+)
unnamed: C39.1, RN16.5 (R4.2)
unnamed: R69.2, U2.3 (EN), U3.7 (PG)
unnamed: R7.2, R8.1, U3.6 (FB)
unnamed: C9.1, U3.8 (SS/TR)
unnamed: R36.1, U21.6 (SDO)
unnamed: R37.1, U21.10 (~IRQ)
unnamed: U27.6 (SCK), U28.56 (QSPI_CLK)
unnamed: U27.5 (SI/IO0), U28.57 (QSPI_SD0)
unnamed: U27.2 (SO/IO1), U28.59 (QSPI_SD1)
unnamed: R39.1, R40.1, U27.1 (~CS), U28.60 (QSPI_SS)
unnamed: U27.7 (~HOLD/IO3), U28.55 (QSPI_SD3)
unnamed: U27.3 (~WP/IO2), U28.58 (QSPI_SD2)
unnamed: R42.1, U28.2 (GPIO_00)
unnamed: R43.1, U28.3 (GPIO_01)
unnamed: S8.3 (2), S8.4 (2), U28.26 (RUN)
unnamed: R51.1, U28.51 (USB_DM)
unnamed: R50.1, U28.52 (USB_DP)
unnamed: L1.2, U28.48 (VREG_LX)
unnamed: R41.2, U28.21 (XIN)
unnamed: C155.1, U28.22 (XOUT), Y1.1
unnamed: R38.2, U35.1, U35.4 (-)
unnamed: C139.1, R38.1, R53.2, U36.4 (-)
unnamed: R52.2, U37.12 (CSB)
unnamed: R10.2, U38.13 (ADR0)
unnamed: R21.2, U38.14 (ADR1)
unnamed: R22.2, U38.15 (INDEP)
unnamed: C220.1, U39.59 (AREG1CAP)
unnamed: C222.1, U39.51 (AREG2CAP)
unnamed: R57.2, R58.1, U39.17 (CONVST_SAR)
unnamed: C221.1, U39.23 (DREGCAP)
unnamed: R16.2, U39.55 (FORMAT0)
unnamed: R31.2, U39.54 (FORMAT1)
unnamed: C14.2, C243.2, R54.2, U39.8 (REF1+), U39.41 (REF2+)
unnamed: C256.2, U39.49 (REF_OUT)
unnamed: U39.34 (~SYNC_OUT), U39.35 (~SYNC_IN)
unnamed: R11.2, U40.13 (ADR0)
unnamed: R23.2, U40.14 (ADR1)
unnamed: R24.2, U40.15 (INDEP)
unnamed: R29.2, U41.13 (ADR0)
unnamed: R30.2, U41.14 (ADR1)
unnamed: R34.2, U41.15 (INDEP)
unnamed: R26.2, U42.13 (ADR0)
unnamed: R27.2, U42.14 (ADR1)
unnamed: R28.2, U42.15 (INDEP)
unnamed: C237.1, R54.1, U45.6 (OUT)
PWRA_GD_NEGATIVE: R5.2, R6.2, R67.2, U28.10 (GPIO_07)
SPI_MISO: J19.7 (DAT0), U24.8 (D3), U28.27 (GPIO_16), U39.21 (DCLK0/SDO)
SPI_MOSI: J19.3 (CMD), U24.6 (D1), U28.31 (GPIO_19), U39.20 (DCLK1/SDI)
SPI_SCLK: J19.5 (CLK), U24.7 (D2), U28.29 (GPIO_18), U39.19 (DCLK2/SCLK)
SPI_~CS_ADC: U28.28 (GPIO_17), U39.18 (ALERT/~CS)
SPI_~CS_SD: J19.2 (DAT3/CD), R59.2, R60.1, U28.32 (GPIO_20)
USBC_VBUS: C2.1, C3.1, C5.1, C7.1, C8.1, C128.1, J6.A4 (VBUS), J6.A9 (VBUS), J6.B4 (VBUS), J6.B9 (VBUS), U1.2 (VIN), U3.2 (VIN), U20.1 (VIN), U20.3 (EN), U31.2 (VIN)
USB_+: J6.A6 (D+), J6.B6 (D+), R50.2
USB_-: J6.A7 (D-), J6.B7 (D-), R51.2
VDDA: C15.1, C16.1, C21.1, C22.1, C29.1, C31.1, C40.1, C41.1, C46.1, C47.1, C54.1, C56.1, C65.1, C66.1, C71.1, C72.1, C79.1, C81.1, C90.1, C91.1, C96.1, C97.1, C104.1, C106.1, C114.1, C115.1, C116.1, C121.1, C122.1, C129.1, C131.1, C137.1, C138.1, C140.1, C141.1, C146.1, C147.1, C154.1, C156.1, C165.1, C166.1, C171.1, C172.1, C179.1, C181.1, C190.1, C191.1, C196.1, C197.1, C204.1, C206.1, C224.1, C226.1, C230.1, C233.1, C236.1, C244.1, C245.1, R5.1, TP8.1, U1.4 (SENSE), U1.5 (VOUT), U4.5 (V+), U5.3 (V_{S+}), U5.7 (~PD), U6.8 (Vs+), U7.3 (V_{S+}), U7.7 (~PD), U8.3 (V_{S+}), U8.7 (~PD), U9.5 (V+), U10.3 (V_{S+}), U10.7 (~PD), U11.8 (Vs+), U12.3 (V_{S+}), U12.7 (~PD), U13.3 (V_{S+}), U13.7 (~PD), U14.5 (V+), U15.3 (V_{S+}), U15.7 (~PD), U16.8 (Vs+), U17.3 (V_{S+}), U17.7 (~PD), U18.5 (V+), U19.8 (Vs+), U22.5 (V+), U23.8 (Vs+), U25.5 (V+), U26.8 (Vs+), U29.5 (V+), U30.8 (Vs+), U32.5 (V+), U34.8 (Vs+), U35.5 (V+), U36.5 (V+), U38.9 (VDD), U40.9 (VDD), U41.9 (VDD), U42.9 (VDD), U44.5 (V+), U45.2 (IN), U54.4 (VDD)
VSSA: C10.1, C17.1, C18.1, C26.1, C27.1, C33.1, C35.1, C42.1, C43.1, C51.1, C52.1, C58.1, C60.1, C67.1, C68.1, C76.1, C77.1, C83.1, C85.1, C92.1, C93.1, C101.1, C102.1, C108.1, C110.1, C117.1, C118.1, C126.1, C127.1, C132.1, C133.1, C134.1, C135.1, C136.1, C142.1, C143.1, C151.1, C152.1, C158.1, C159.1, C160.1, C167.1, C168.1, C176.1, C177.1, C183.1, C185.1, C192.1, C193.1, C201.1, C202.1, C208.1, C210.1, C215.2, C228.2, C229.2, C232.2, C235.1, R6.1, TP2.1, U2.5 (VOUT), U4.2 (V-), U5.6 (V_{S-}), U6.5 (Vs-), U7.6 (V_{S-}), U8.6 (V_{S-}), U9.2 (V-), U10.6 (V_{S-}), U11.5 (Vs-), U12.6 (V_{S-}), U13.6 (V_{S-}), U14.2 (V-), U15.6 (V_{S-}), U16.5 (Vs-), U17.6 (V_{S-}), U18.2 (V-), U19.5 (Vs-), U22.2 (V-), U23.5 (Vs-), U25.2 (V-), U26.5 (Vs-), U29.2 (V-), U30.5 (Vs-), U32.2 (V-), U34.5 (Vs-), U35.2 (V-), U36.2 (V-), U38.5 (VSS), U38.17 (EXP), U40.5 (VSS), U40.17 (EXP), U41.5 (VSS), U41.17 (EXP), U42.5 (VSS), U42.17 (EXP), U44.2 (V-), U54.7 (VSS)

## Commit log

2026-02-23 Add the .gitignore file to the project
2026-02-23 Files for hardware version 2 added. Includes Kicad files, firmware, and the Python API.
2026-02-24 Change the project structure; fix some unit tests
2026-02-24 Changed the firmware for the AD7779 to the unified version from the Pico Runtime Library repository.
2026-02-24 Change the path to a generic one
2026-05-12 Update with GitLab last push
